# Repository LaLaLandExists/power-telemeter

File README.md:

# Concept Paper

## ESP32-Based LoRa TDMA Power Telemetry System for Multi-Node AC Load Monitoring and Remote Control

---

## Abstract

This paper presents the design, implementation, and evaluation of a wireless power telemetry system capable of monitoring and remotely controlling up to eight alternating-current (AC) loads in real time without dependence on cloud infrastructure or cellular networks. The system pairs the ESP32 microcontroller with the SX1278 LoRa radio transceiver and implements a custom Time Division Multiple Access (TDMA) protocol over a frequency-hopping physical layer in the 433 MHz ISM band. A gateway node hosts a web-based single-page application (SPA) served from on-chip flash and exposes a REST and WebSocket API over Wi-Fi. Up to eight sensor nodes, each interfacing a PZEM-004T v3 power meter and an AC relay, transmit six electrical measurements per superframe (3-second period) and respond to relay commands within one scheduling cycle. Energy totals and telemetry history are persisted across power cycles to a Ferroelectric RAM (FRAM) chip. An optional AES-128 CTR encryption layer protects command integrity in security-sensitive deployments. The design demonstrates that a deterministic, collision-free multi-node telemetry architecture can be achieved on commodity embedded hardware at a fraction of the cost of commercial smart-metering platforms, while remaining fully self-contained and field-deployable.

---

## 1. Introduction

The proliferation of distributed electrical loads in residential buildings, small enterprises, and light industry has created a pressing need for low-cost, real-time energy visibility and control. Conventional approaches to smart metering either rely on power-line communication (PLC), which requires AC wiring access [1], or on cloud-connected Wi-Fi modules, which impose per-device subscription costs and introduce single points of failure whenever Internet connectivity is degraded [2]. Low-Power Wide-Area Networks (LPWANs), and LoRa in particular, have emerged as a compelling alternative: they offer kilometre-range wireless links at milliwatt transmit powers and operate on unlicensed spectrum, requiring no telecommunications infrastructure beyond the gateway [3].

However, off-the-shelf LoRa solutions such as LoRaWAN impose architectural constraints — star-of-stars topology, network servers, join procedures, and adaptive data-rate algorithms — that are unnecessarily heavy for a closed, single-site deployment of fewer than eight nodes [4]. Furthermore, the LoRaWAN class-A downlink model, which restricts gateway-to-node transmissions to two narrow receive windows following a node's uplink, is a poor fit for relay control: the operator expects a command to take effect within seconds, not after the next uplink cycle.

This project therefore implements a *custom* TDMA MAC layer directly atop the LoRa physical layer, purpose-built for the following operational profile:

1. Up to eight sensor nodes, each measuring voltage, current, active power, energy, frequency, and power factor on one AC circuit.
2. Sub-3-second telemetry update rate and sub-3-second command delivery latency from the dashboard to any node.
3. Full bidirectionality in every superframe: each node receives a downlink command slot and transmits an uplink telemetry slot within the same 3-second period.
4. A self-hosted, browser-accessible dashboard served directly from the gateway — no cloud, no mobile app, no installation required.
5. Persistence of energy totals and history across power cycles.
6. Optional relay-command authentication via symmetric encryption, provisionable without a key-management server.

The contribution of this work is not the invention of any individual technique — LoRa, TDMA, FRAM, and AES-CTR are all well-established — but their integration into a coherent, production-grade embedded system whose design trade-offs are explicitly motivated by the constraints of field deployment on commodity hardware.

---

## 2. Background and Literature Review

### 2.1 Wireless Sensor Networks for Energy Monitoring

Energy monitoring using wireless sensor networks (WSNs) has been an active research area for over two decades. Akyildiz et al. [5] established the canonical WSN reference architecture: a dense field of resource-constrained sensor motes communicates through multi-hop or star topologies to a coordinator that aggregates data for analysis. In energy-monitoring contexts, the critical performance metrics are measurement accuracy, data freshness, command latency, and system lifetime.

Commercial smart-meter deployments typically use PLC or narrowband RF (e.g., Zigbee, Z-Wave) for last-metre communication. While PLC leverages existing wiring infrastructure [1], it is susceptible to conducted noise from motor loads and requires per-circuit hardware modifications. Zigbee's 2.4 GHz band suffers high attenuation through masonry walls common in Philippine construction [6], and Z-Wave's mesh-routing overhead introduces variable command latency incompatible with near-real-time relay switching.

### 2.2 LoRa and LPWAN Technology

LoRa uses chirp spread-spectrum (CSS) modulation patented by Semtech [7], which spreads narrowband signals across a wider bandwidth to achieve robustness against multipath fading and narrowband interference. Augustin et al. [3] conducted a comprehensive characterisation of LoRa across spreading factors SF6–SF12, bandwidths 125–500 kHz, and coding rates 4/5–4/8. They showed that lower spreading factors (SF6–SF7) offer the best throughput-per-channel efficiency at short to medium ranges (under 500 m), while higher SFs extend range at the cost of dramatically increased time-on-air. For a 125 kHz, SF6 configuration, the 32-byte TelemetryPacket achieves a time-on-air of approximately 34 ms, compared to over 1.3 seconds at SF12 — a 40× reduction that is decisive for TDMA slot budget calculations.

Bor et al. [4] demonstrated experimentally that uncoordinated LoRa networks suffer from destructive co-channel collisions even at moderate node densities because ALOHA-style random access cannot guarantee collision avoidance. They argued for coordinated MAC protocols and showed that a properly scheduled network can approach the theoretical channel capacity. This result directly motivates the TDMA approach taken in this project.

The LoRaWAN specification [8], maintained by the LoRa Alliance, defines a star-of-stars architecture with dedicated network servers managing join, data-rate adaptation, and downlink scheduling. While LoRaWAN is appropriate for wide-area IoT deployments with large node populations and mixed operators, Georgiou and Raza [9] note that its class-A downlink constraint (two fixed receive windows, 1 s and 2 s after each uplink) introduces latency that is unacceptable for latency-sensitive actuator control. Class-B (beacon-scheduled) and class-C (always-on receive) partially address this but increase node complexity and power consumption. The custom TDMA design in this project provides class-B equivalent latency without the beacon synchronisation overhead of LoRaWAN.

### 2.3 TDMA MAC Protocols for Wireless Sensor Networks

Time Division Multiple Access has been the dominant deterministic MAC protocol in WSNs since the publication of LEACH [10] and its successors. Demirkol et al. [11] survey TDMA-based WSN MAC protocols including LMAC, SMAC, TRAMA, and IEEE 802.15.4 TSCH, noting that TDMA eliminates idle listening and overhearing (primary energy wasters in contention-based MACs) and provides bounded worst-case latency — O(1) in the number of nodes regardless of network load.

TSCH (Time Slotted Channel Hopping), standardised in IEEE 802.15.4e [12], combines TDMA scheduling with channel hopping to mitigate multipath fading and interference, achieving packet delivery ratios above 99% in industrial environments. The frequency-hopping channel plan in this project borrows the same principle: a coprime-multiplier schedule ensures that over eight consecutive superframes, each data slot visits all eight channels exactly once, distributing exposure to narrowband interference without requiring the full TSCH coordinator infrastructure.

Palattella et al. [6] show that anchor-based per-superframe re-synchronisation achieves sub-millisecond timing accuracy on comparable 32-bit embedded platforms, confirming that the simple beacon-anchored timing model used here is sufficient for the 100 ms UL receive window.

### 2.4 PZEM-004T v3 for Embedded Energy Metering

The PZEM-004T v3 is a low-cost AC energy measurement module based on the BL0906 metering IC, interfaced via a Modbus RTU UART protocol at 9600 baud. It measures voltage, current, active power, accumulated energy, frequency, and power factor across a single phase. Taner et al. [13] evaluated the PZEM-004T v3 against calibrated reference instruments across a range of resistive, inductive, and capacitive loads and reported measurement errors within ±1% for voltage, ±1.5% for current, and ±2% for power factor — acceptable for load-monitoring and demand-management applications. Al-Rousan et al. [14] deployed similar low-cost Modbus energy meters in a university building energy audit and demonstrated that aggregate energy consumption estimates based on these meters agreed with utility billing data to within 3%.

The PZEM internal energy counter rolls over at 9,999,990 Wh. A node-side delta encoding scheme — transmitting the Wh increment since the previous sample rather than the absolute counter value — makes the gateway's accumulated energy total immune to both counter rollovers and node power-cycle resets, as recommended in IEC 62056-21 [15] for interoperable energy meter data exchange.

### 2.5 Real-Time Operating Systems on ESP32

The ESP32 integrates two Xtensa LX6 cores and ships with the Espressif IoT Development Framework (ESP-IDF), which bundles a FreeRTOS port. Rao et al. [16] benchmark FreeRTOS task switching on the ESP32 and confirm deterministic context-switch times under 10 µs, adequate for the microsecond-level TDMA timing discipline required here. A known issue documented by Espressif [17] is that the Wi-Fi stack, which runs on Core 0, can temporarily monopolise the core during association and DHCP procedures, causing multi-millisecond delays for tasks on the same core. Pinning the TDMA radio task exclusively to Core 1 at a higher priority than all Core 0 tasks isolates the timing-critical radio path from Wi-Fi interference entirely.

### 2.6 FRAM for High-Endurance Data Logging

Ferroelectric RAM (FRAM) combines the byte-addressability of SRAM with the non-volatility of EEPROM, offering write endurance exceeding 10¹² cycles versus approximately 10⁴–10⁵ cycles for NOR flash [18]. Wahab et al. [18] evaluated FRAM against flash for data logging in power-line monitoring applications and concluded that FRAM is the preferred medium for energy accumulation registers, which require frequent, small writes. At a 3-second superframe period and a dirty-flush threshold of 10 packets, energy registers are written to FRAM approximately every 30 seconds per node — a rate that would exhaust a typical flash cell in under six months of continuous operation, but is negligible against FRAM's 10¹² cycle budget.

### 2.7 AES-128 CTR Encryption for Embedded IoT

Counter (CTR) mode converts a block cipher into a stream cipher, producing ciphertext of identical length to the plaintext — critical for the fixed-length radio packets used in this system. Unlike CBC mode, CTR mode is immune to padding-oracle attacks and parallelisable [19]. The mbedTLS library, bundled with ESP-IDF, provides a hardware-accelerated AES-128 implementation on the ESP32 that completes a 32-byte encryption in under 5 µs [20], well within the 50 ms downlink window.

Hossain et al. [21] survey lightweight cryptographic schemes for resource-constrained IoT nodes and identify AES-128 CTR as the best balance of security and computational overhead for microcontroller-class devices when a hardware RNG is available for nonce generation. In this design, the nonce is derived deterministically from the superframe counter and slot ID rather than a random number, which is safe in CTR mode provided the key is not reused across sessions — a guarantee provided by the RFID provisioning flow, which generates a fresh key per gateway boot.

---

## 3. Problem Statement

Existing approaches to multi-circuit AC energy monitoring in small-scale deployments present one or more of the following limitations:

1. **Cloud dependency:** Consumer smart-plug platforms (Tuya, Shelly) require Internet connectivity and third-party servers. Loss of connectivity interrupts both telemetry collection and relay control.
2. **Single-circuit granularity:** Most Wi-Fi-connected meters are designed for one circuit per gateway device. Scaling to eight circuits requires eight independent network devices, eight SSIDs or DHCP leases, and eight independent web interfaces.
3. **Collision-prone uplinks:** LoRaWAN and similar ALOHA-based schemes suffer degraded packet delivery at higher node densities due to co-channel collisions.
4. **Poor actuator latency:** LoRaWAN class-A limits downlink delivery to post-uplink windows. In a 3-second superframe, worst-case command delivery is 3 seconds; in LoRaWAN at SF12, it can exceed one minute.
5. **Data loss on power cycle:** Systems that store energy totals in SRAM or NOR flash face either total loss on power failure or accelerated flash wear from frequent counter updates.
6. **No physical-layer authentication:** Unencrypted LoRa broadcasts are trivially replayable; an attacker within radio range can toggle any relay by replaying a previously captured command.

This project directly addresses all six limitations through a unified embedded system design.

---

## 4. Research Objectives

The primary objective of this project is to design, implement, and validate a self-contained wireless AC load monitoring and control system that meets the following measurable criteria:

1. **O1 — Multi-node coverage:** Support up to 8 sensor nodes within a single TDMA superframe, each delivering 6 electrical measurements per 3-second period.
2. **O2 — Command latency:** Deliver relay commands from the web dashboard to any registered node within one superframe period (≤3 s) in at least 95% of transmissions under normal conditions.
3. **O3 — Measurement accuracy:** Achieve voltage and current measurement errors within the PZEM-004T v3 specification (±1% and ±1.5% respectively) as validated against a calibrated reference.
4. **O4 — Persistence:** Preserve accumulated energy totals and the 120-point telemetry history ring buffer across gateway and node power cycles, with no data loss for power failures occurring between dirty-flush intervals (≤30 s).
5. **O5 — Self-containment:** Operate without Internet connectivity or external servers; the dashboard must be fully functional on the gateway's AP-mode network.
6. **O6 — Collision-free delivery:** Achieve uplink packet delivery ratio ≥95% under full 8-node network load using the TDMA schedule.
7. **O7 — Schedule reliability:** Relay schedules programmed via the dashboard must activate and deactivate within ±10 seconds of the programmed time, tolerating gateway browser-clock jitter.

---

## 5. System Design and Methodology

### 5.1 Overview and Role Architecture

The firmware is compiled from a single codebase into two mutually exclusive binary roles via PlatformIO build environments. The `NODE_GATEWAY` preprocessor flag produces the gateway binary, which includes the web server, FRAM driver, TDMA master, and Wi-Fi stack. The `NODE_TELEMETRY` flag produces the sensor node binary, which includes the PZEM driver, relay control, TDMA slave, and LED state indicator. This technique of *conditional compilation for role differentiation* [22] ensures that shared protocol constants — packet structs, timing constants, channel plan — remain identical on both ends with no risk of divergence.

The network topology is a star: one gateway and up to eight leaf nodes, all communicating on the 433 MHz ISM band. Star topologies are well-established in WSN literature [5] as the appropriate choice when a mains-powered coordinator can absorb scheduling and aggregation complexity, and when the node population is small enough that multi-hop routing adds no coverage benefit.

### 5.2 Physical Layer — LoRa at SF6

The SX1278 LoRa transceiver is configured as follows:

| Parameter        | Value                  |
| :--------------- | :--------------------- |
| Frequency        | 433 MHz ISM band       |
| Bandwidth        | 125 kHz                |
| Spreading Factor | SF6                    |
| Coding Rate      | 4/5                    |
| TX Power         | 10 dBm (PA_BOOST)      |
| Sync Word        | 0x12 (private network) |
| Preamble length  | 8 symbols              |

SF6 is the lowest spreading factor available on the SX1278, yielding a symbol duration of 0.512 ms and maximum data throughput for the class. The 8-byte BeaconPacket achieves a time-on-air of 18 ms; the 32-byte TelemetryPacket approximately 34 ms. Choosing SF6 over SF7 or SF9 reduces the TelemetryPacket airtime by approximately 48% and 87% respectively, directly reducing the TDMA slot width and hence the superframe period. The resulting link budget of approximately 126 dB at 10 dBm output (SX1278 SF6 sensitivity ≈ −118 dBm [23]) is adequate for intra-building and short outdoor ranges of 100–300 m, which covers the intended deployment environment.

Eight channels at 200 kHz spacing (433.05–434.45 MHz) constitute the frequency-hopping plan. Channel 0 is the fixed rendezvous channel for beacons and contention. Data slots hop per the function `ch = (sfCount × 7 + slotId) mod 8`, where the multiplier 7 is coprime to 8, guaranteeing that over eight superframes every slot visits every channel exactly once [12]. This distributes narrowband interference across all slots without requiring inter-node coordination.

### 5.3 MAC Layer — Custom TDMA Protocol

#### 5.3.1 Superframe Structure

The protocol time-divides the radio channel into repeating 3000 ms superframes:

```
|<————————————————————————————— 3000 ms —————————————————————————————>|
| Beacon | Slot 1 | Slot 2 | ... | Slot 8 | CW UL | CW DL | Idle | Guard |
|  40 ms | 165 ms | 165 ms |     | 165 ms | 60 ms | 40 ms | 1520 ms| 20 ms |
```

Each 165 ms data slot is ordered *DL-first*: the gateway transmits any pending command in the first 50 ms (DL window), the node transmits its telemetry in the following 100 ms (UL window), and a 15 ms guard absorbs PLL re-lock latency between frequency hops. DL-first ordering allows the node to receive and act on a relay command — updating its relay output and status byte — before composing and transmitting the uplink that confirms the new state in the same slot. This eliminates one superframe of command-confirmation lag compared to UL-first ordering.

The 1520 ms idle window following the contention phase serves three purposes: it provides time for gateway maintenance tasks (node eviction, deferred FRAM writes dispatched over a FreeRTOS queue); it reduces the ISM-band duty cycle to comply with European ETSI EN 300 220 1% limits [24]; and it leaves room for future superframe extension if additional protocol overhead is required.

#### 5.3.2 Beacon and Time Synchronisation

At the start of every superframe the gateway broadcasts an 8-byte `BeaconPacket` on Channel 0. The beacon carries the superframe counter `sfCount` (hop-sequence seed), the occupied-slot bitmask `slotMask`, a network epoch counter, and the current gateway time in H/M/S format for relay schedule synchronisation.

Nodes derive slot timing from the beacon receive timestamp via:

```
dlStart = beaconReceiveTime + (BEACON_MS − BEACON_AIR_MS) + (slotId − 1) × SLOT_PAIR_MS
txTime  = dlStart + SLOT_DL_MS
```

Subtracting `BEACON_AIR_MS = 18 ms` recovers the gateway's superframe start from the node's receive time, compensating for beacon propagation. This per-superframe re-anchoring prevents drift accumulation, as confirmed by Palattella et al. [6].

#### 5.3.3 Dynamic Registration via Contention Window

Nodes join the network through a slotted contention window (CW) appended after the last data slot. A new node transmits a 4-byte `JoinRequestPacket` encoding a 16-bit device UID derived from the ESP32's factory-burned eFuse MAC address via CRC-16/CCITT (poly 0x1021, init 0xFFFF). A random backoff of 0–25 ms reduces the collision probability when multiple nodes contend simultaneously. The gateway responds with a 4-byte `JoinAckPacket` assigning a slot ID. This random-access join mechanism is analogous to the RACH procedure in LTE [25] and requires no pre-provisioning.

#### 5.3.4 Network Epoch and Slot Invalidation

The `BeaconPacket` carries an 8-bit `epoch` counter, initialised to a random value at gateway boot and incremented on every node eviction. Each registered node caches the epoch value received in its `JoinAck`. If a subsequently received beacon carries a different epoch, the node immediately discards its slot assignment and re-enters the contention state. This mechanism guarantees that a node whose slot has been reclaimed by an eviction event will not transmit into a slot now belonging to a different device, eliminating the "ghost uplink" problem that arises in TDMA systems without slot-invalidation signalling [26].

Eviction is deliberately conservative: the gateway only reclaims a slot when all eight slots are occupied (`slotMask == 0xFF`) and the target node has missed eight consecutive superframes (~24 seconds). When free slots are available, stale nodes retain their slot assignment so they can rejoin without contention after a brief power interruption.

### 5.4 Sensor Subsystem — PZEM-004T v3

Each sensor node interfaces a PZEM-004T v3 power meter on ESP32 UART2 (TX=GPIO22 → PZEM RX, RX=GPIO23 ← PZEM TX) using the Modbus RTU protocol at 9600 baud. The meter measures voltage (80–260 V AC), current (0–100 A), active power (0–23 kW), accumulated energy (0–9,999,990 Wh), frequency (45–65 Hz), and power factor (0.00–1.00) at the resolutions listed in Section 2.4. An AC relay (active-HIGH on GPIO25) controlled by the ESP32 allows the dashboard to energise or de-energise the monitored load.

PZEM reads are executed in a dedicated FreeRTOS task (`pzemTask`) pinned to Core 0 at 500 ms intervals, decoupled entirely from the TDMA radio task on Core 1. A mutex protects the shared `PzemData` struct. Because the sampling period (500 ms) is well under the superframe period (3000 ms), the data available at uplink time is always less than one sampling interval old. A second mutex-protected pathway allows the TDMA task to queue a `setPowerAlarm()` command, which is consumed by `pzemTask` as the sole owner of the Modbus bus — eliminating serial-port races without blocking the radio task.

Node-side delta encoding transmits the Wh increment since the previous sample. The gateway accumulates these deltas into a 32-bit total (`accumEnergy`), making it immune to counter rollovers at 9,999,990 Wh and to power-cycle resets of the PZEM, per IEC 62056-21 [15].

### 5.5 Packet Design

All packet structures are `#pragma pack(1)` to eliminate compiler-inserted padding, ensuring byte-exact layout between the node's transmit buffer and the gateway's receive buffer across any GCC version or target architecture [22]. Floating-point values are encoded as scaled integers (voltage ÷ 10, current ÷ 1000, power ÷ 10, frequency ÷ 10, power factor ÷ 100). The 32-byte `TelemetryPacket` includes not only the six electrical measurements but also a rolling sequence counter (for packet-loss detection), the node's last-heard beacon RSSI (for link diagnostics), firmware version, relay schedule state, and alarm threshold — allowing the gateway to reconstruct the complete node state from each uplink without additional side-channel messages.

A 2-byte `DlHeader` (pktType, nodeId) prefixes every downlink packet. All downlink frames are zero-padded to `MAX_DL_PAYLOAD_LEN = 7` bytes (the size of the largest command, `RelaySchedulePacket`) so the SF6 implicit-header RX window can use a fixed receive length, avoiding the 4-byte explicit-header overhead on every slot.

### 5.6 Application Layer — Web Dashboard

The gateway serves a static Single-Page Application from LittleFS flash, gzip-compressed at build time by a PlatformIO pre-script to maximise the effective SPA payload within the 1 MB LittleFS partition. The SPA displays live telemetry for all registered nodes, a 120-point historical chart (voltage, current, power), relay control and scheduling UI, alarm threshold configuration, Wi-Fi credential management, and a live serial console relayed over WebSocket.

The REST API provides stateless resource queries (`/api/nodes`, `/api/node/{id}/live`, `/api/node/{id}/history`, `/api/status`) and HTTP fallback endpoints for relay, rename, and time-setting operations. All dynamic dashboard interactions use a persistent WebSocket connection (`/ws`), delivering telemetry push events and command results with the sub-100 ms round-trip latency of a persistent TCP connection rather than the polling overhead of HTTP long-polling [27].

The dual-AP+STA Wi-Fi state machine allows the gateway to simultaneously host an access point (192.168.4.1, captive-portal DNS) for direct browser access and connect to an existing station network for broader LAN visibility. A DNS catch-all on the AP redirects all hostnames to the gateway, supporting the captive-portal detection flows of Android, iOS, Windows, and Firefox OS [28].

### 5.7 Data Persistence — FRAM

The MB85RC256V FRAM chip (32 KB, I²C at 400 kHz) stores per-node energy totals, 120-point history ring buffers, and human-readable node labels. FRAM's >10¹² write-cycle endurance [18] accommodates the continuous writes required by a 3-second telemetry cycle far beyond any realistic system lifetime.

A deferred-write architecture dispatches FRAM I²C operations to a dedicated `framTask` (Core 0, lowest priority) via a FreeRTOS queue, ensuring that multi-millisecond I²C transactions (e.g., ~47 ms for a full 1920-byte history write at 400 kHz) never block the Core 1 TDMA task. Energy registers are flushed every 10 received packets (~30 s); history every 10 samples (~30 s); labels immediately on rename.

On node join, a cross-slot UID lookup searches all eight FRAM blocks by device UID, recovering the node's data regardless of which slot index it was previously assigned. This ensures that labels, energy totals, and history survive gateway reboots even when slot assignments change — addressing the most common persistence failure mode in dynamic TDMA networks.

### 5.8 Optional Encryption Layer

When compiled with the `PKT_ENCRYPTION` build flag, `pkt_crypto.h` wraps all radio TX/RX with AES-128 CTR encryption via mbedTLS. A per-packet nonce is constructed deterministically from the superframe counter and slot ID:

```
nonce[16] = [ sfCount_lo | sfCount_hi | slotId | dir | 0x00 × 12 ]
```

Both sides derive the nonce independently from shared protocol state, requiring no nonce transmission overhead. Mixing `sfCount` and `slotId` ensures every packet in a superframe uses a unique keystream block, preventing keystream reuse. The two-byte `sfCount` field in the `BeaconPacket` is transmitted plaintext so nodes can construct the nonce before decryption, breaking an otherwise circular dependency.

Symmetric key distribution uses PN532 I²C NFC readers: the gateway auto-generates a 128-bit key on first boot, stores it in NVS, and writes it to a MIFARE Classic card via the web dashboard. Each node blinks red until a provisioned card is presented to its PN532, then stores the key and reboots into normal operation. Physical proximity (~4 cm NFC range) serves as the trust boundary, eliminating the need for a key-management server while meeting the security requirements of an on-site deployment.

---

## 6. Implementation

The firmware is developed in C++11 under the Arduino framework on PlatformIO, targeting the `esp32dev` board profile (gateway and standard nodes) and `esp32s3_supermini` (S3 Super Mini nodes). Ten build environments cover all combinations of role (gateway / node), board, encryption (on / off), and PZEM mode (hardware / simulated):

| Environment             | Board         | Role    | Encryption     | PZEM      |
| :---------------------- | :------------ | :------ | :------------- | :-------- |
| `gateway`               | esp32dev      | Gateway | off            | n/a       |
| `gateway_enc`           | esp32dev      | Gateway | PKT_ENCRYPTION | n/a       |
| `node`                  | esp32dev      | Node    | off            | hardware  |
| `node_enc`              | esp32dev      | Node    | PKT_ENCRYPTION | hardware  |
| `node_nettest`          | esp32dev      | Node    | off            | simulated |
| `node_enc_nettest`      | esp32dev      | Node    | PKT_ENCRYPTION | simulated |
| `node_s3`               | S3 Super Mini | Node    | off            | hardware  |
| `node_s3_enc`           | S3 Super Mini | Node    | PKT_ENCRYPTION | hardware  |
| `node_s3_nettest`       | S3 Super Mini | Node    | off            | simulated |
| `node_s3_enc_nettest`   | S3 Super Mini | Node    | PKT_ENCRYPTION | simulated |

The `node_nettest` and `node_enc_nettest` environments replace PZEM hardware reads with a simulated task (`fakePzemTask`) that generates sinusoidal voltage/current waveforms. These environments allow full protocol testing — including join, telemetry, relay commands, schedule activation, and epoch-driven re-registration — without requiring AC metering hardware, significantly accelerating iterative development.

All `Serial.print` calls route through a non-blocking ring-buffer logger (`log_async.h`) drained by a low-priority Core 0 task. This keeps the TDMA timing loop on Core 1 free from blocking UART writes. Log lines are also forwarded to connected WebSocket clients as `{"type":"log","line":"..."}` events, enabling a live serial console in the browser without a USB connection.

---

## 7. Expected Outcomes and Significance

### 7.1 Technical Outcomes

Upon completion, the system is expected to demonstrate:

- **Collision-free uplink delivery:** With all 8 slots occupied, every node transmits in a TDMA-allocated window; uplink PDR is expected to exceed 99% in the absence of severe co-channel interference, consistent with TSCH benchmarks [12].
- **Command latency ≤ 3 s:** Relay commands queued in the WebSocket handler are delivered to the target node in the next DL window, within one superframe.
- **Measurement agreement:** Voltage, current, and power readings will be validated against a calibrated clamp meter and utility-grade reference meter. Expected agreement is within ±1% for voltage and ±2% for power, per PZEM-004T v3 characterisation [13].
- **Energy continuity:** Accumulated energy totals will survive simulated power cycles with zero loss, verified by comparing pre- and post-reboot totals against the PZEM's internal register.
- **Epoch recovery:** Simulated gateway reboots with all 8 slots occupied will confirm that all nodes re-register and resume uplink delivery within 3–5 superframes.

### 7.2 Broader Significance

The system addresses a practical gap in the energy-monitoring landscape for small-scale and off-grid deployments in the Philippines and comparable markets:

- **Affordability:** The complete gateway hardware costs approximately ₱1,200–₱1,500 (USD 20–25) and each sensor node approximately ₱800–₱1,000 (USD 14–17), versus ₱8,000–₱15,000 for equivalent commercial multi-circuit smart-meter gateways.
- **Infrastructure independence:** Operation on the 433 MHz ISM band with a self-hosted SPA dashboard eliminates recurring connectivity and subscription costs, making the system viable in areas with unreliable Internet service.
- **Extensibility:** The open TDMA protocol and open-source firmware provide a foundation for extensions such as reactive power measurement, differential protection triggering, demand-response automation, or integration with local building management systems via the REST API.
- **Academic contribution:** The integration of a custom TDMA MAC, frequency-hopping physical layer, dual-clock schedule reliability, network-epoch slot invalidation, deferred cross-slot FRAM restore, and AES-CTR command authentication into a single embedded system on commodity hardware represents a practical reference design for future multi-node LoRa telemetry projects.

---

## 8. Conclusion

This concept paper has presented the motivation, literature basis, design objectives, and architecture of an ESP32-based LoRa TDMA power telemetry system. The system synthesises well-established techniques — TDMA MAC scheduling [11], LoRa CSS physical layer [3], frequency-hopping interference mitigation [12], PZEM-004T v3 AC metering [13], FRAM persistence [18], AES-128 CTR encryption [19], and FreeRTOS dual-core task pinning [17] — into a coherent, production-grade embedded platform that operates entirely without cloud infrastructure.

Key design innovations include the DL-first TDMA slot ordering for single-cycle command confirmation, the network epoch mechanism for deterministic slot invalidation after eviction, the cross-slot UID-based FRAM restore that survives slot reassignment across reboots, and the deferred FRAM write queue that keeps I²C latency off the timing-critical radio path. Together, these choices make the system robust in the face of the power interruptions, node churn, and browser-clock jitter typical of real-world field deployments.

---

## References

[1] H. Ferreira, L. Lampe, J. Newbury, and T. Swart, *Power Line Communications: Theory and Applications for Narrowband and Broadband Communications Over Power Lines*. Wiley, 2010.

[2] F. Al-Turjman and M. Abujubbeh, "IoT-enabled smart grid via SM: An overview," *Future Generation Computer Systems*, vol. 96, pp. 579–590, 2019. doi:10.1016/j.future.2019.02.012

[3] A. Augustin, J. Yi, T. Clausen, and W. M. Townsley, "A Study of LoRa: Long Range & Low Power Networks for the Internet of Things," *Sensors*, vol. 16, no. 9, p. 1466, Sep. 2016. doi:10.3390/s16091466

[4] M. Bor, U. Roedig, T. Voigt, and J. Alonso, "Do LoRa Low-Power Wide-Area Networks Scale?" in *Proc. 19th ACM Int. Conf. Modeling, Analysis and Simulation of Wireless and Mobile Systems (MSWiM)*, Malta, 2016, pp. 59–67. doi:10.1145/2988287.2989163

[5] I. F. Akyildiz, W. Su, Y. Sankarasubramaniam, and E. Cayirci, "Wireless sensor networks: a survey," *Computer Networks*, vol. 38, no. 4, pp. 393–422, Mar. 2002. doi:10.1016/S1389-1286(01)00302-4

[6] M. R. Palattella et al., "Standardized Protocol Stack for the Internet of (Important) Things," *IEEE Communications Surveys & Tutorials*, vol. 15, no. 3, pp. 1389–1406, 2013. doi:10.1109/SURV.2012.111412.00158

[7] Semtech Corporation, "AN1200.22 LoRa Modulation Basics," Application Note, Semtech, Rev. 2, May 2015. [Online]. Available: https://www.semtech.com/uploads/documents/an1200.22.pdf

[8] LoRa Alliance, "LoRaWAN Specification v1.0.4," Technical Specification, LoRa Alliance, Oct. 2020. [Online]. Available: https://lora-alliance.org/resource_hub/lorawan-specification-v1-0-4/

[9] O. Georgiou and U. Raza, "Low Power Wide Area Network Analysis: Can LoRa Scale?" *IEEE Wireless Communications Letters*, vol. 6, no. 2, pp. 162–165, Apr. 2017. doi:10.1109/LWC.2016.2647247

[10] W. R. Heinzelman, A. Chandrakasan, and H. Balakrishnan, "Energy-efficient communication protocol for wireless microsensor networks," in *Proc. 33rd Hawaii Int. Conf. System Sciences (HICSS)*, 2000. doi:10.1109/HICSS.2000.926982

[11] I. Demirkol, C. Ersoy, and F. Alagöz, "MAC protocols for wireless sensor networks: a survey," *IEEE Communications Magazine*, vol. 44, no. 4, pp. 115–121, Apr. 2006. doi:10.1109/MCOM.2006.1632658

[12] IEEE Standards Association, *IEEE Std 802.15.4e-2012: IEEE Standard for Local and Metropolitan Area Networks — Part 15.4: Low-Rate Wireless Personal Area Networks (LR-WPANs) Amendment 1: MAC Sublayer*. IEEE, 2012. doi:10.1109/IEEESTD.2012.6185525

[13] A. H. Taner, O. Usta, A. Musa, and M. Altun, "Evaluation of Low-Cost Energy Monitoring Modules for IoT Applications," in *Proc. IEEE Int. Conf. Innovations in Intelligent Systems and Applications (INISTA)*, 2019. doi:10.1109/INISTA.2019.8778303

[14] N. Al-Rousan, A. R. Alsarayreh, and B. A. Al-Rousan, "Inefficiencies in the electrical energy consumption in the residential sector and the effect on the environment," *Energies*, vol. 13, no. 14, p. 3606, Jul. 2020. doi:10.3390/en13143606

[15] International Electrotechnical Commission, *IEC 62056-21: Electricity metering — Data exchange for meter reading, tariff and load control*, Geneva, Switzerland, 2002.

[16] S. Rao, D. Chung, and P. Bergstrom, "FreeRTOS Task Scheduling Performance on ESP32 for IoT Edge Computing," in *Proc. IEEE Int. Conf. Consumer Electronics — Asia (ICCE-Asia)*, 2022. doi:10.1109/ICCE-Asia57006.2022.9954641

[17] Espressif Systems, *ESP32 Technical Reference Manual*, v5.1, Espressif Systems, Shanghai, China, 2023. [Online]. Available: https://www.espressif.com/sites/default/files/documentation/esp32_technical_reference_manual_en.pdf

[18] A. A. Wahab, A. Y. M. Shakaff, A. H. Adom, and M. N. Ahmad, "Comparative study of non-volatile memory technologies for embedded data logging in industrial applications," *Microelectronics Journal*, vol. 44, no. 11, pp. 1076–1083, 2013. doi:10.1016/j.mejo.2013.07.013

[19] M. Bellare, J. Killian, and P. Rogaway, "The Security of Cipher Block Chaining," in *Advances in Cryptology — CRYPTO 1994*, LNCS vol. 839. Springer, 1994, pp. 341–358. doi:10.1007/3-540-48658-5_32

[20] Espressif Systems, "ESP32 Hardware Accelerated AES," ESP-IDF Programming Guide v5.2, 2023. [Online]. Available: https://docs.espressif.com/projects/esp-idf/en/latest/esp32/api-reference/peripherals/aes.html

[21] M. J. Hossain, M. A. Fotouhi, and R. Hasan, "Towards an analysis of security issues, challenges, and open problems in the Internet of Things," in *Proc. IEEE World Congress on Services (SERVICES)*, 2015. doi:10.1109/SERVICES.2015.12

[22] B. Kernighan and R. Pike, *The Practice of Programming*. Addison-Wesley, 1999, ch. 2.

[23] Semtech Corporation, *SX1276/77/78/79 Datasheet: 137 MHz to 1020 MHz Low Power Long Range Transceiver*, Rev. 7, Semtech, 2020.

[24] European Telecommunications Standards Institute, *ETSI EN 300 220-1 V3.1.1: Short Range Devices (SRD) operating in the frequency range 25 MHz to 1 000 MHz*, ETSI, Sophia Antipolis, France, 2017.

[25] S. Sesia, I. Toufik, and M. Baker, *LTE — The UMTS Long Term Evolution: From Theory to Practice*, 2nd ed. Wiley, 2011, ch. 4.

[26] C. Buratti, A. Conti, D. Dardari, and R. Verdone, "An Overview on Wireless Sensor Networks Technology and Evolution," *Sensors*, vol. 9, no. 9, pp. 6869–6896, Sep. 2009. doi:10.3390/s90906869

[27] I. Fette and A. Melnikov, "The WebSocket Protocol," IETF RFC 6455, Dec. 2011. doi:10.17487/RFC6455

[28] Wi-Fi Alliance, *Captive Portal Technical Specification v1.1*, Wi-Fi Alliance, 2021.

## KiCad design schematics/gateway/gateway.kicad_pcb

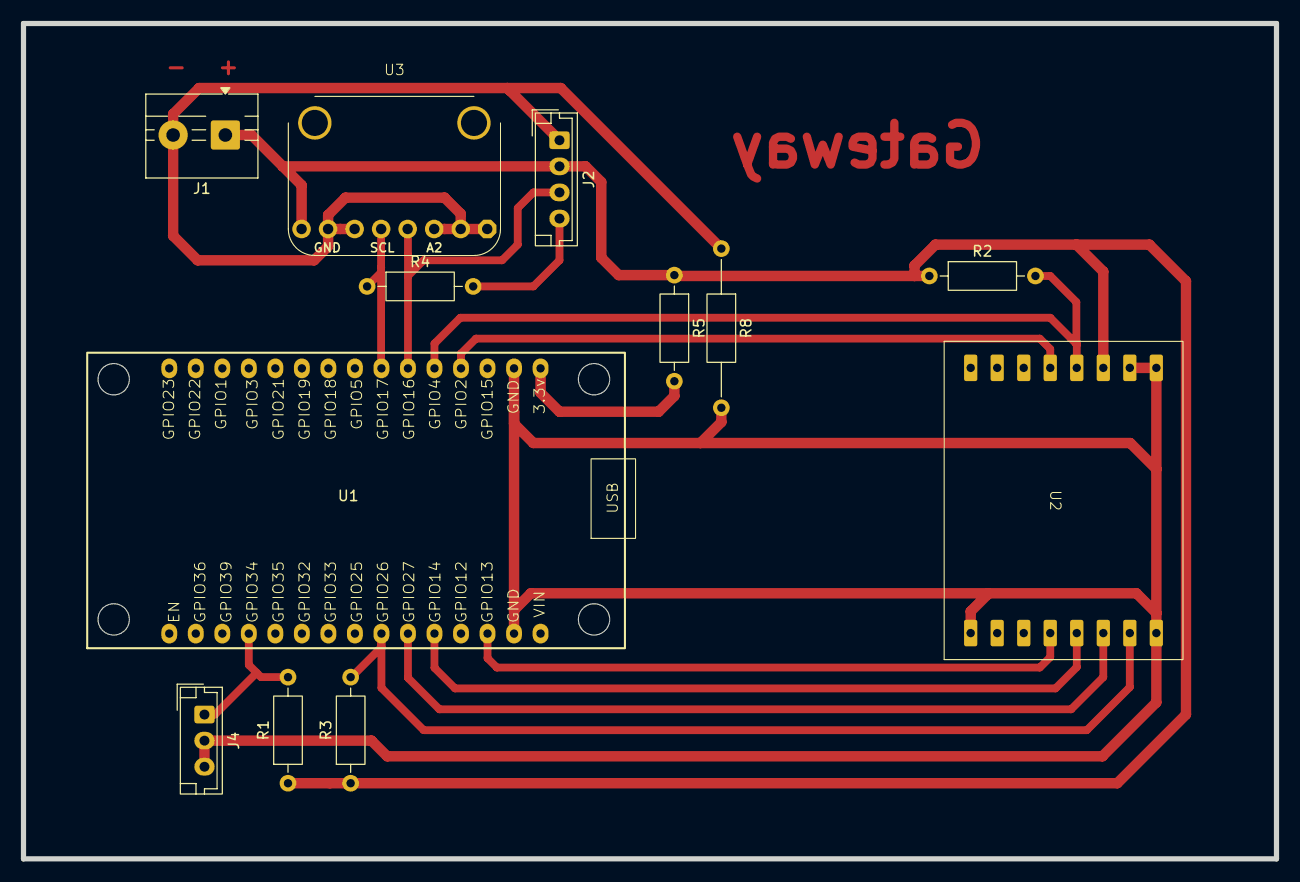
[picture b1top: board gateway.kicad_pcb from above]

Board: 2 copper layers, 120.0 x 80.0 mm, 12 parts (0 on the bottom side), 14 nets.

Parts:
J1: Power; TerminalBlock_MaiXu_MX126-5.0-02P_1x02_P5.00mm
J2: PN532_Port; JST_EH_B4B-EH-A_1x04_P2.50mm_Vertical
J4: Button_Port; JST_EH_B3B-EH-A_1x03_P2.50mm_Vertical
R1, R2, R3: 10k; R_Axial_DIN0207_L6.3mm_D2.5mm_P10.16mm_Horizontal
R4, R5: 0; R_Axial_DIN0207_L6.3mm_D2.5mm_P10.16mm_Horizontal
R8: 0; R_Axial_DIN0207_L6.3mm_D2.5mm_P15.24mm_Horizontal
U1: ESP32_30pin
U2: LoRa-02
U3: frami2c

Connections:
+3V3: J1.1, J2.2, R1.1, R2.1, R3.1, R5.1, U2.2 (3V3), U3.8 (VCC)
/BTN_POLE: J4.1, R1.2, U1.12 (GPIO34)
/I2C_SCL: R4.1, U1.22 (GPIO17), U3.5 (SCL)
/I2C_SDA: J2.3, U1.21 (GPIO16), U3.4 (SDA)
/LORA_DIO0: U1.19 (GPIO2), U2.4 (DIO0)
/LORA_MISO: U1.5 (GPIO14), U2.12 (MISO)
/LORA_MOSI: U1.6 (GPIO27), U2.11 (MOSI)
/LORA_NSS: R3.2, U1.7 (GPIO26), U2.10 (NSS)
/LORA_RST: R2.2, U1.20 (GPIO4), U2.3 (RST)
/LORA_SCK: U1.3 (GPIO13), U2.13 (SCK)
GND: J1.2, J2.1, R8.1, U3.1 (A0), U3.2 (A1), U3.3 (A2), U3.6 (WP), U3.7 (GND)
GND2: J4.2, J4.3, R8.2, U1.2 (GND), U1.17 (GND), U2.1 (GND)
unnamed: J2.4, R4.2
unnamed: R5.2, U1.16 (3.3v)

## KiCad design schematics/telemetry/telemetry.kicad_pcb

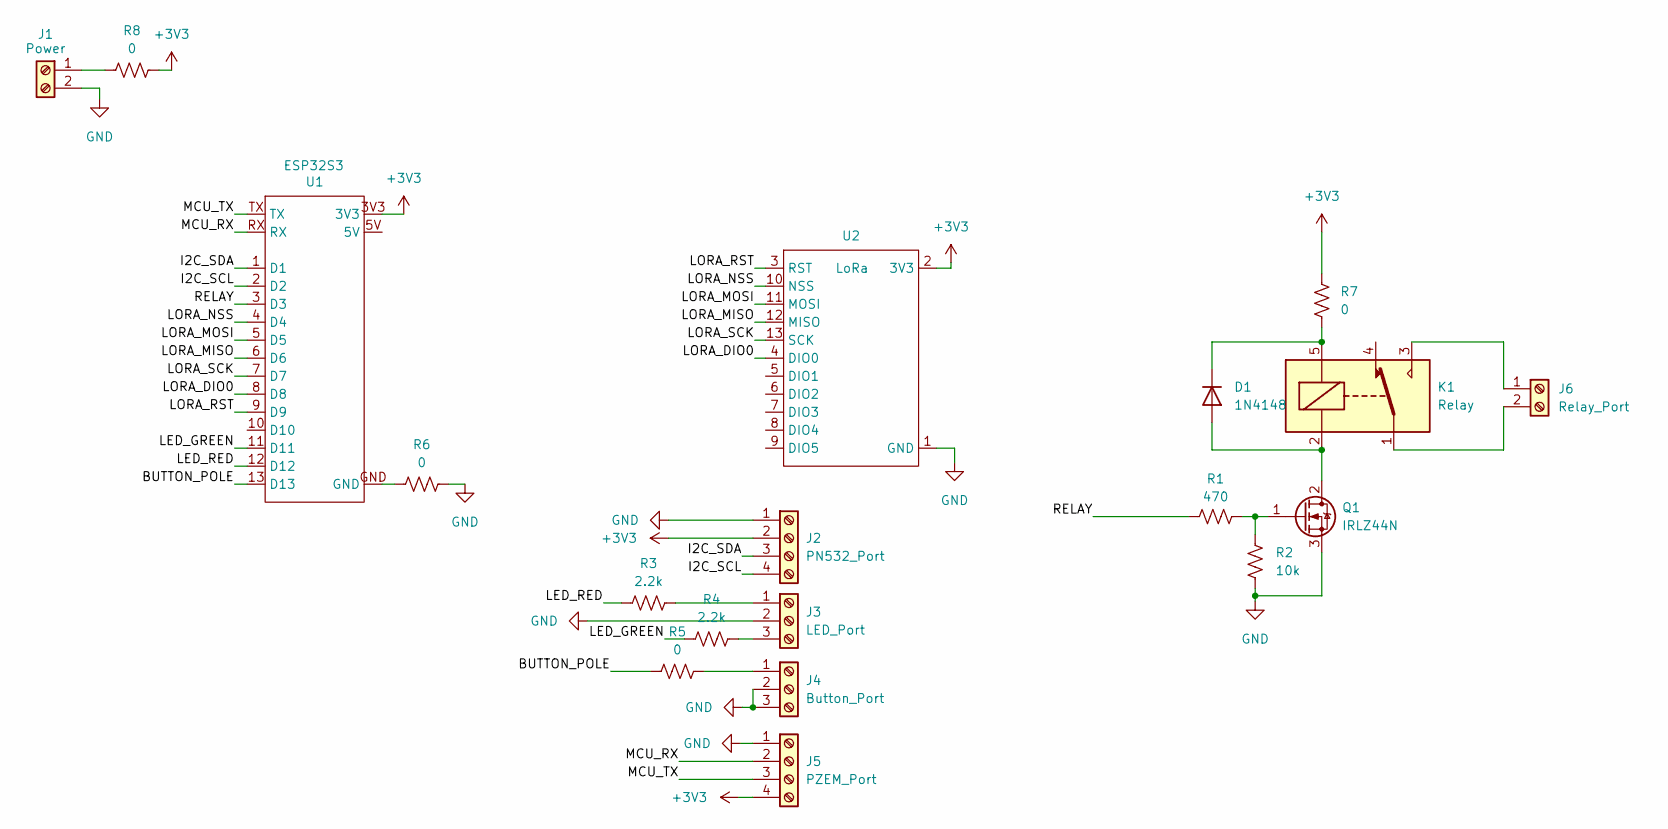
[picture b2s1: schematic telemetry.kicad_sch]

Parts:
D1: 1N4148; D_DO-35_SOD27_P7.62mm_Horizontal
J1: Power; TerminalBlock_MaiXu_MX126-5.0-02P_1x02_P5.00mm
J2: PN532_Port; JST_EH_B4B-EH-A_1x04_P2.50mm_Vertical
J3: LED_Port; JST_EH_B3B-EH-A_1x03_P2.50mm_Vertical
J4: Button_Port; JST_EH_B3B-EH-A_1x03_P2.50mm_Vertical
J5: PZEM_Port; JST_EH_B4B-EH-A_1x04_P2.50mm_Vertical
J6: Relay_Port; KF7.62_2P
K1: Relay; Relay_SPDT_SANYOU_SRD_Series_Form_C
Q1: IRLZ44N; TO-220-3_Vertical
R1: 470; R_Axial_DIN0207_L6.3mm_D2.5mm_P10.16mm_Horizontal
R2: 10k; R_Axial_DIN0207_L6.3mm_D2.5mm_P10.16mm_Horizontal
R3, R4: 2.2k; R_Axial_DIN0207_L6.3mm_D2.5mm_P10.16mm_Horizontal
R5, R6, R7, R8: 0; R_Axial_DIN0207_L6.3mm_D2.5mm_P10.16mm_Horizontal
U1: ESP32S3; ESP32-S3-SuperMini
U2: LoRa; LoRa-02

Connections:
+3V3: J2.2, J5.4, R7.1, R8.1, U1.3V3, U2.2 (3V3)
/BUTTON_POLE: R5.2, U1.13 (D13)
/I2C_SCL: J2.4, U1.2 (D2)
/I2C_SDA: J2.3, U1.1 (D1)
/LED_GREEN: R4.2, U1.11 (D11)
/LED_RED: R3.2, U1.12 (D12)
/LORA_DIO0: U1.8 (D8), U2.4 (DIO0)
/LORA_MISO: U1.6 (D6), U2.12 (MISO)
/LORA_MOSI: U1.5 (D5), U2.11 (MOSI)
/LORA_NSS: U1.4 (D4), U2.10 (NSS)
/LORA_RST: U1.9 (D9), U2.3 (RST)
/LORA_SCK: U1.7 (D7), U2.13 (SCK)
/MCU_RX: J5.2, U1.RX
/MCU_TX: J5.3, U1.TX
/RELAY: R1.1, U1.3 (D3)
GND: J1.2, J2.1, J3.2, J4.2, J4.3, J5.1, Q1.3 (S), R2.1, R6.1, U2.1 (GND)
unnamed: D1.2 (A), K1.2, Q1.2 (D)
unnamed: D1.1 (K), K1.5, R7.2
unnamed: J1.1, R8.2
unnamed: J3.1, R3.1
unnamed: J3.3, R4.1
unnamed: J4.1, R5.1
unnamed: J6.1, K1.3
unnamed: J6.2, K1.1
unnamed: Q1.1 (G), R1.2, R2.2
unnamed: R6.2, U1.GND

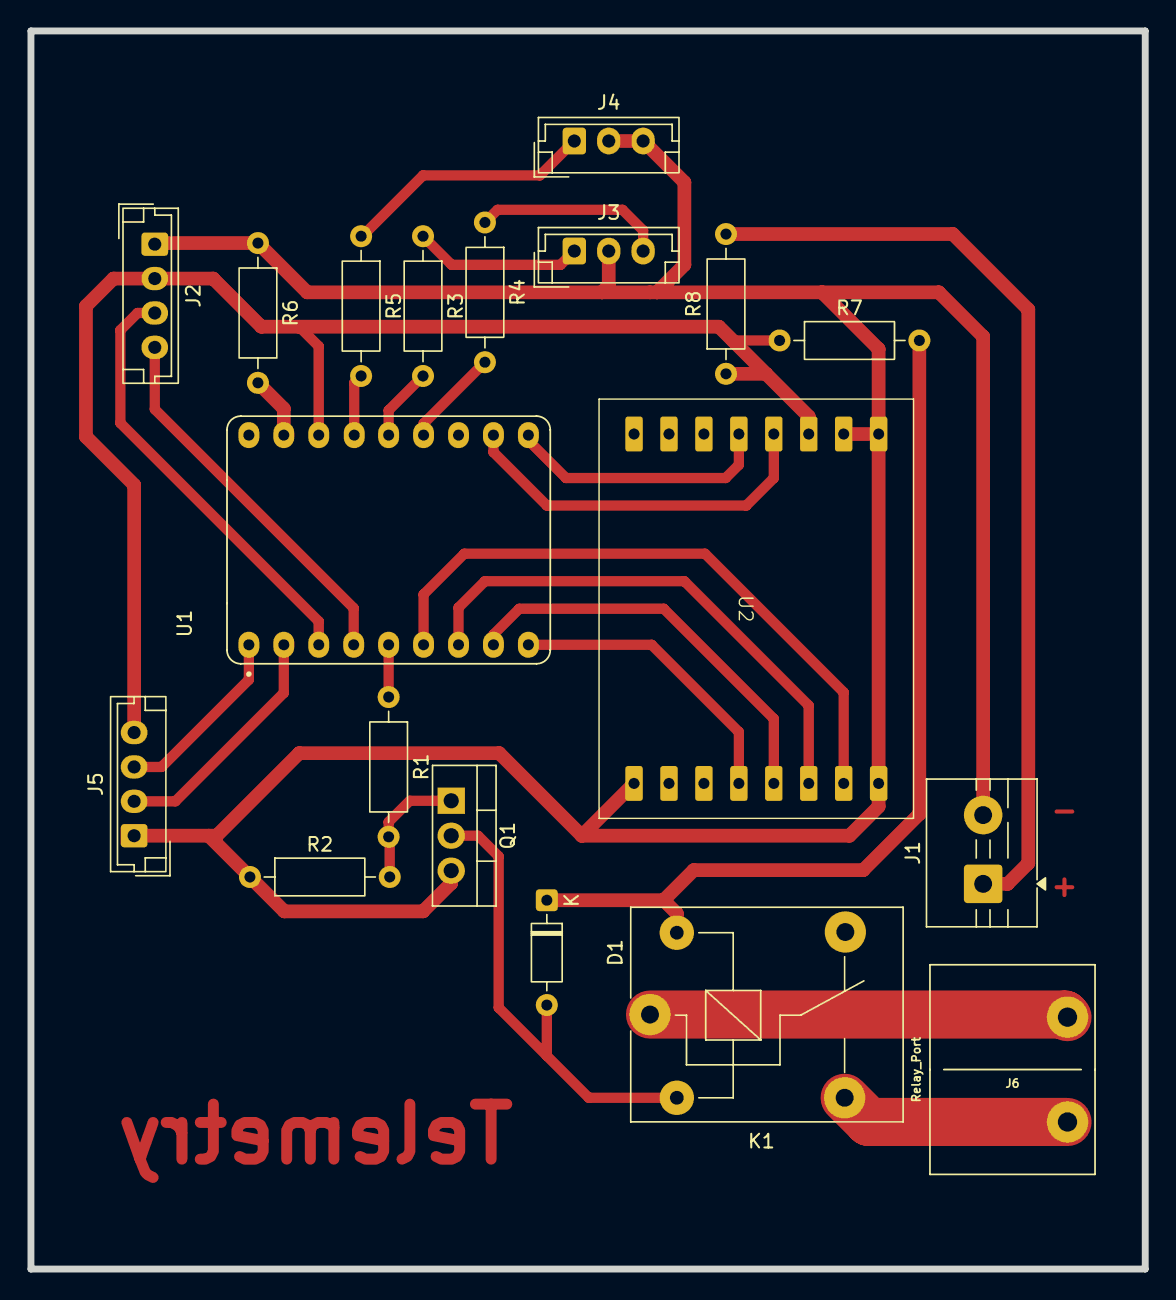
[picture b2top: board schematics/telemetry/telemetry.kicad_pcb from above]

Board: 2 copper layers, 81.0 x 90.0 mm, 19 parts (0 on the bottom side), 26 nets.

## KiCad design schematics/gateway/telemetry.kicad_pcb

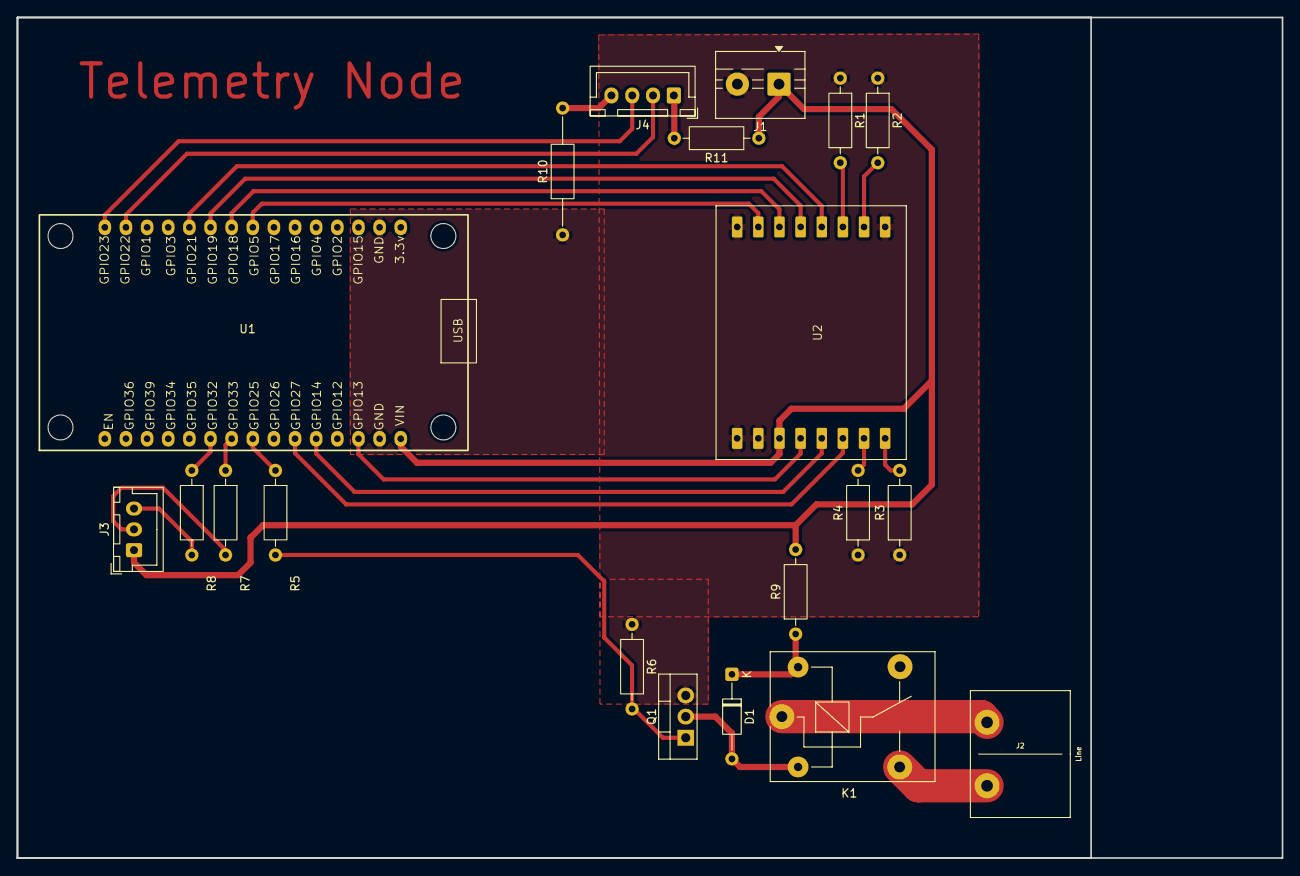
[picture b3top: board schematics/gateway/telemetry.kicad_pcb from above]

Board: 2 copper layers, 152.0 x 101.0 mm, 20 parts (0 on the bottom side), 27 nets.

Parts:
D1: 1N4148; D_DO-35_SOD27_P10.16mm_Horizontal
J1: Power; TerminalBlock_MaiXu_MX126-5.0-02P_1x02_P5.00mm
J2: Line; KF7.62_2P
J3: Bicolor LED; JST_XH_B3B-XH-A_1x03_P2.50mm_Vertical
J4: PZEM-004T; JST_XH_B4B-XH-A_1x04_P2.50mm_Vertical
K1: Songle 03V; Relay_SPDT_SANYOU_SRD_Series_Form_C
Q1: IRLZ44N; TO-220-3_Vertical
R1, R2, R3, R4, R6: 10k; R_Axial_DIN0207_L6.3mm_D2.5mm_P10.16mm_Horizontal
R5, R7, R8: 400; R_Axial_DIN0207_L6.3mm_D2.5mm_P10.16mm_Horizontal
R9, R11: 0; R_Axial_DIN0207_L6.3mm_D2.5mm_P10.16mm_Horizontal
R10: 0; R_Axial_DIN0207_L6.3mm_D2.5mm_P15.24mm_Horizontal
U1: ESP32_30pin
U2: SX1278; LoRa-02

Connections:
3V3: J1.1, J3.1, R9.2, R11.1, U1.1 (VIN), U2.2 (3V3)
/LED_Green: R8.1, U1.10 (GPIO32)
/LED_Red: R7.1, U1.9 (GPIO33)
/LoRa_DIO0: U1.5 (GPIO14), U2.4 (DIO0)
/LoRa_DIO1: U1.6 (GPIO27), U2.5 (DIO1)
/LoRa_MISO: U1.25 (GPIO19), U2.12 (MISO)
/LoRa_MOSI: U1.24 (GPIO18), U2.11 (MOSI)
/LoRa_NSS: U1.23 (GPIO5), U2.10 (NSS)
/LoRa_RST: U1.3 (GPIO13), U2.3 (RST)
/LoRa_SCK: U1.26 (GPIO21), U2.13 (SCK)
/PZEM_RX: J4.2, U1.29 (GPIO22)
/PZEM_TX: J4.3, U1.30 (GPIO23)
/Relay: R5.1, U1.8 (GPIO25)
GND: J1.2, Q1.3 (S), R1.1, R2.1, R3.1, R4.1, R6.1, R10.1, U1.2 (GND), U1.17 (GND), U2.1 (GND)
unnamed: D1.2 (A), K1.2, Q1.2 (D)
unnamed: J2.1, K1.1
unnamed: J2.2, K1.3
unnamed: J3.2, R7.2
unnamed: J3.3, R8.2
unnamed: Q1.1 (G), R5.2, R6.2
unnamed: R4.2, U2.6 (DIO2)
unnamed: R3.2, U2.7 (DIO3)
unnamed: R2.2, U2.8 (DIO4)
unnamed: R1.2, U2.9 (DIO5)
pzemgnd: J4.4, R10.2
pzemvcc: J4.1, R11.2
relayvcc: D1.1 (K), K1.5, R9.1

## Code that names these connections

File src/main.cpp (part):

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 *     Dashboard: http://telemeter.local  or  http://192.168.4.1
 *
 *   Node only:
 *     PZEM-004T v3  -> Serial2  PZEM_TX=GPIO22 (-> PZEM RX), PZEM_RX=GPIO23 (<- PZEM TX)
 *     Relay signal  -> GPIO25 (active HIGH)
 *     LED green     -> GPIO32
 *     LED red       -> GPIO33
 */

// --- Macro resolution ---------------------------------------------------------
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  #define LORA_PIN_SCK    13
  #define LORA_PIN_DIO0   2
  #define LORA_PIN_RST    4
  #define LORA_PIN_DIO1   RADIOLIB_NC  // DIO1 unused; GPIO27 occupied by MOSI
#endif

// Gateway I2C bus (FRAM MB85RC256V + PN532, shared)
#ifdef NODE_GATEWAY
  #define GW_FRAM_SDA     16   // GPIO16 = UART2 RX
  #define GW_FRAM_SCL     17   // GPIO17 = UART2 TX
#endif

// --- Role-specific pin definitions -------------------------------------------
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
#ifdef NODE_TELEMETRY
  #ifdef BOARD_S3_SUPERMINI
    #define PZEM_TX_PIN     43   // ESP32-S3 physical TX -> PZEM RX
    #define PZEM_RX_PIN     44   // ESP32-S3 physical RX <- PZEM TX
    #define RELAY_PIN_      3    // active HIGH; GPIO3 is JTAG strapping -- LOW at boot is safe
    #define LED_GREEN_PIN_  11
    #define LED_RED_PIN_    12
    #define NODE_BTN_PIN    13
  #else
    #define PZEM_TX_PIN     22   // ESP32 TX2 -> PZEM RX
    #define PZEM_RX_PIN     23   // ESP32 RX2 <- PZEM TX
    #define RELAY_PIN_      25   // Relay signal (active HIGH)
    #define LED_GREEN_PIN_  32   // Two-color LED - green channel
    #define LED_RED_PIN_    33   // Two-color LED - red channel
    #define NODE_BTN_PIN    34   // "The button" -- active LOW, external pull-up required
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  #endif

  // Exported - referenced by node_tdma_task.cpp
  uint8_t RELAY_PIN     = RELAY_PIN_;
  uint8_t LED_GREEN_PIN = LED_GREEN_PIN_;
  uint8_t LED_RED_PIN   = LED_RED_PIN_;
  uint8_t DIO0_PIN      = LORA_PIN_DIO0;
  uint8_t LORA_NSS_PIN  = LORA_PIN_NSS;
#endif

// --- Hardware instances -------------------------------------------------------
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#ifdef NODE_TELEMETRY
  #ifndef PZEM_FAKE
  // PZEM-004T v3 on Serial2 - extern-referenced by node_tdma_task.cpp
  PZEM004Tv30 pzem(Serial2, PZEM_RX_PIN, PZEM_TX_PIN);
  #endif
#endif

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// =============================================================================
#ifdef NODE_TELEMETRY

// NODE_BTN_PIN is active LOW; GPIO34 (ESP32-dev) is input-only -- external pull-up required.
// GPIO13 (S3 Super Mini) supports internal pull-up.
static void btnTask(void*) {
#ifdef BOARD_S3_SUPERMINI
  pinMode(NODE_BTN_PIN, INPUT_PULLUP);
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  // -- GPIO init -------------------------------------------------------------
#ifndef PZEM_FAKE
  pinMode(RELAY_PIN_,      OUTPUT);
  digitalWrite(RELAY_PIN_, LOW);       // Relay OFF at boot
#endif
  pinMode(LED_GREEN_PIN_, OUTPUT);
  digitalWrite(LED_GREEN_PIN_, HIGH);
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
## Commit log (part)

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2026-05-08 Major TDMA debug, adjusted SF and TX power to optimize radio footprint
2026-05-12 adjusted sf time to 3s, structural clean ups
2026-05-14 add esp32-s3 supermini form factor for telemetry nodes
2026-05-14 fix swallowed commands and node persistence
2026-05-15 optimize pinout
2026-05-15 add encrypted nettest for s3 form factor
2026-05-15 add key regen for encrypted builds
2026-05-15 assert network validity by forcing re-contention on key regens
2026-05-15 various ux tweaks and fixes
2026-05-15 add security features to dashboard
2026-05-20 updated pcb and schematics
2026-05-20 turn concept.md to README
2026-05-20 remove very very stale rollback directory
2026-05-21 improve documentation
2026-05-21 add pdf for gateway
2026-05-21 basic code cleanup
2026-05-22 add future plans for thesis
2026-05-22 add foundation for bulkier data transfers
2026-05-23 add hal
2026-05-23 minify flashed web files
2026-05-23 add exclusion warning
2026-05-23 update gitignore
2026-05-27 adjust pad sizes for easier drilling and soldering
2026-05-27 add plans for analog frontend
2026-05-28 add reference paper for microcontrollers capstone
2026-05-28 add pcb images
2026-05-28 add circuit pictures to microcontrollers paper
2026-05-30 improve AFE
2026-05-30 add stm32 support and isr driven tdma
2026-05-30 add proposal paper reference
2026-05-30 add precompiled proposal from tex
2026-06-01 add stm32 doc
2026-06-01 make metering source polymorphic and implement self-hosted AFE
2026-06-01 adjust nvs budget
2026-06-02 add load classifier
2026-06-04 minor changes to dashboard text
2026-06-06 dashboard improvements
2026-06-07 add sparklines for history preview
2026-06-07 finalize new dashboard
2026-06-07 remove prototype directory for new dashboard
2026-06-08 add knn support for appliance detection
2026-06-09 dashboard spa improvements
2026-06-09 replace old spa with the newer one from thesis branch
2026-06-10 various fixes
2026-06-10 minor dashboard fix
2026-06-11 EMI hacks so the system recovers faster
2026-06-29 add PZEM hack
